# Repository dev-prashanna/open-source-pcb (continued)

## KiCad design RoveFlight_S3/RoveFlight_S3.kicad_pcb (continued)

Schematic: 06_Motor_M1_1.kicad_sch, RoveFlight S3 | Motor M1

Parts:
C110: 100nF; C_0402_1005Metric_RF_C110; MPN GRM155R71C104KA88D
D3: SS24; D_SMA; MPN SS24-13-F
J3: M1 MOTOR; MotorPads; MPN PCB_SOLDER_PADS_24AWG
Q3: AO3400A; SOT-23; MPN AO3400A
R109: 100; R_0402_1005Metric_RF_R109; MPN RC0402FR-071000L
R110: 10k; R_0402_1005Metric_RF_R110; MPN RC0402FR-071002L
R111: 100k; R_0402_1005Metric_RF_R111; MPN RC0402FR-071003L

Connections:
BUF_M1: R109.1; also elsewhere on the board
GATE_M1: Q3.1 (G), R109.2, R110.1
GND: C110.2, Q3.2 (S), R110.2, R111.2; also elsewhere on the board
M1_NEG: D3.2 (A), J3.2, Q3.3 (D)
PWM_M1: R111.1; also elsewhere on the board
VM: C110.1, D3.1 (K), J3.1; also elsewhere on the board

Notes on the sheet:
1S BRUSHED ONLY. Pin1 VM+, pin2 switched motor negative. 1A running / 2A brief stall target. 100R gate resistor; 10k gate-source pulldown; SS24 flyback cathode VM, anode drain. Fit additional 100nF directly at motor terminals; twist leads. Rotation is set by motor wiring.

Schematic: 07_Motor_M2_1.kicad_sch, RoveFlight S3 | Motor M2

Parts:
C111: 100nF; C_0402_1005Metric_RF_C111; MPN GRM155R71C104KA88D
D4: SS24; D_SMA; MPN SS24-13-F
J4: M2 MOTOR; MotorPads; MPN PCB_SOLDER_PADS_24AWG
Q4: AO3400A; SOT-23; MPN AO3400A
R112: 100; R_0402_1005Metric_RF_R112; MPN RC0402FR-071000L
R113: 10k; R_0402_1005Metric_RF_R113; MPN RC0402FR-071002L
R114: 100k; R_0402_1005Metric_RF_R114; MPN RC0402FR-071003L

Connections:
BUF_M2: R112.1; also elsewhere on the board
GATE_M2: Q4.1 (G), R112.2, R113.1
GND: C111.2, Q4.2 (S), R113.2, R114.2; also elsewhere on the board
M2_NEG: D4.2 (A), J4.2, Q4.3 (D)
PWM_M2: R114.1; also elsewhere on the board
VM: C111.1, D4.1 (K), J4.1; also elsewhere on the board

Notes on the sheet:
1S BRUSHED ONLY. Pin1 VM+, pin2 switched motor negative. 1A running / 2A brief stall target. 100R gate resistor; 10k gate-source pulldown; SS24 flyback cathode VM, anode drain. Fit additional 100nF directly at motor terminals; twist leads. Rotation is set by motor wiring.

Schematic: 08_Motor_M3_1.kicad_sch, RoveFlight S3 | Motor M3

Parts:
C112: 100nF; C_0402_1005Metric_RF_C112; MPN GRM155R71C104KA88D
D5: SS24; D_SMA; MPN SS24-13-F
J5: M3 MOTOR; MotorPads; MPN PCB_SOLDER_PADS_24AWG
Q5: AO3400A; SOT-23; MPN AO3400A
R115: 100; R_0402_1005Metric_RF_R115; MPN RC0402FR-071000L
R116: 10k; R_0402_1005Metric_RF_R116; MPN RC0402FR-071002L
R117: 100k; R_0402_1005Metric_RF_R117; MPN RC0402FR-071003L

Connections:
BUF_M3: R115.1; also elsewhere on the board
GATE_M3: Q5.1 (G), R115.2, R116.1
GND: C112.2, Q5.2 (S), R116.2, R117.2; also elsewhere on the board
M3_NEG: D5.2 (A), J5.2, Q5.3 (D)
PWM_M3: R117.1; also elsewhere on the board
VM: C112.1, D5.1 (K), J5.1; also elsewhere on the board

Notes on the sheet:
1S BRUSHED ONLY. Pin1 VM+, pin2 switched motor negative. 1A running / 2A brief stall target. 100R gate resistor; 10k gate-source pulldown; SS24 flyback cathode VM, anode drain. Fit additional 100nF directly at motor terminals; twist leads. Rotation is set by motor wiring.

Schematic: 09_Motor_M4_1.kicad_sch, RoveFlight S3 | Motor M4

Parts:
C113: 100nF; C_0402_1005Metric_RF_C113; MPN GRM155R71C104KA88D
D6: SS24; D_SMA; MPN SS24-13-F
J6: M4 MOTOR; MotorPads; MPN PCB_SOLDER_PADS_24AWG
Q6: AO3400A; SOT-23; MPN AO3400A
R118: 100; R_0402_1005Metric_RF_R118; MPN RC0402FR-071000L
R119: 10k; R_0402_1005Metric_RF_R119; MPN RC0402FR-071002L
R120: 100k; R_0402_1005Metric_RF_R120; MPN RC0402FR-071003L

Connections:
BUF_M4: R118.1; also elsewhere on the board
GATE_M4: Q6.1 (G), R118.2, R119.1
GND: C113.2, Q6.2 (S), R119.2, R120.2; also elsewhere on the board
M4_NEG: D6.2 (A), J6.2, Q6.3 (D)
PWM_M4: R120.1; also elsewhere on the board
VM: C113.1, D6.1 (K), J6.1; also elsewhere on the board

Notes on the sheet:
1S BRUSHED ONLY. Pin1 VM+, pin2 switched motor negative. 1A running / 2A brief stall target. 100R gate resistor; 10k gate-source pulldown; SS24 flyback cathode VM, anode drain. Fit additional 100nF directly at motor terminals; twist leads. Rotation is set by motor wiring.

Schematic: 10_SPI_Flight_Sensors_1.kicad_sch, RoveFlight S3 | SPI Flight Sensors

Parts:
C114: 100nF; C_0402_1005Metric_RF_C114; MPN GRM155R71C104KA88D
C115: 100nF; C_0402_1005Metric_RF_C115; MPN GRM155R71C104KA88D
C116: 1uF; C_0402_1005Metric_RF_C116; MPN GRM155R61A105KE15D
C117: 100nF; C_0402_1005Metric_RF_C117; MPN GRM155R71C104KA88D
C118: 100nF; C_0402_1005Metric_RF_C118; MPN GRM155R71C104KA88D
U8: BMI270; Bosch_LGA-14_3x2.5mm_P0.5mm; MPN BMI270
U9: BMP390; BMP390_LGA10; MPN BMP390

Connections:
+3V3_SENS: C114.1, C115.1, C116.1, C117.1, C118.1, U8.5 (VDDIO), U8.8 (VDD), U9.1 (VDDIO), U9.10 (VDD); also elsewhere on the board
BARO_CS: U9.6 (CSB); also elsewhere on the board
GND: C114.2, C115.2, C116.2, C117.2, C118.2, U8.6 (GNDIO), U8.7 (GND), U9.3 (GND), U9.8 (GND), U9.9 (GND); also elsewhere on the board
IMU_CS: U8.12 (CSB); also elsewhere on the board
IMU_INT: U8.4 (INT1); also elsewhere on the board
SPI_MISO: U8.1 (SDO), U9.5 (SDO); also elsewhere on the board
SPI_MOSI: U8.14 (SDI), U9.4 (SDI); also elsewhere on the board
SPI_SCK: U8.13 (SCK), U9.2 (SCK); also elsewhere on the board

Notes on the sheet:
BMI270 primary 4-wire SPI, INT1 data ready. Auxiliary/OIS pins intentionally NC. BMP390 on shared SPI with independent CS; INT unused. Pressure port faces underside. No compass: motor conductors are too close for a defensible uncalibrated onboard heading.

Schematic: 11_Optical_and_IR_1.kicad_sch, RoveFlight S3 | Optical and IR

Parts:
C119: 100nF; C_0402_1005Metric_RF_C119; MPN GRM155R71C104KA88D
C120: 4.7uF; C_0603_1608Metric; MPN GRM188R60J475KE19D
C121: 1uF; C_0402_1005Metric_RF_C121; MPN GRM155R61A105KE15D
C122: 100nF; C_0402_1005Metric_RF_C122; MPN GRM155R71C104KA88D
R121: 10k; R_0402_1005Metric_RF_R121; MPN RC0402FR-071002L
R122: 10k; R_0402_1005Metric_RF_R122; MPN RC0402FR-071002L
R123: 2.2k; R_0402_1005Metric_RF_R123; MPN RC0402FR-072201L
R124: 2.2k; R_0402_1005Metric_RF_R124; MPN RC0402FR-072201L
R125: 100; R_0402_1005Metric_RF_R125; MPN RC0402FR-071000L
U10: VL53L1CXV0FY/1; ST_VL53L1x; MPN VL53L1CXV0FY/1
U11: TSOP75438TT; MPN TSOP75438TT

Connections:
+3V3: R125.1; also elsewhere on the board
+3V3_SENS: C119.1, C120.1, R121.1, R122.1, R123.1, R124.1, U10.1 (AVDDVCSEL), U10.11 (AVDD); also elsewhere on the board
GND: C119.2, C120.2, C121.2, C122.2, U10.2 (AVSSVCSEL), U10.3 (GND), U10.4 (GND), U10.6 (GND), U10.12 (GND), U11.1 (GND), U11.4 (GND); also elsewhere on the board
I2C_SCL: R124.2, U10.10 (SCL); also elsewhere on the board
I2C_SDA: R123.2, U10.9 (SDA); also elsewhere on the board
IR_RX: U11.3 (OUT); also elsewhere on the board
IR_VS: C121.1, C122.1, R125.2, U11.2 (VS)
TOF_INT: R122.2, U10.7 (GPIO1); also elsewhere on the board
TOF_XSHUT: R121.2, U10.5 (XSHUT); also elsewhere on the board

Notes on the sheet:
VL53L1X faces DOWN, I2C 0x29. Firmware must enable 2V8 I/O mode for 3V3 supply. Use near-ground ranging only; sunlight, reflective floors, tilt and prop wash limit reliability. TSOP75438TT is a 38kHz receiver, not proximity sensing. Optical flow is an external SPI module.

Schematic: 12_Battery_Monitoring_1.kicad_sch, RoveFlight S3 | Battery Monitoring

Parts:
C123: 100nF; C_0402_1005Metric_RF_C123; MPN GRM155R71C104KA88D
C124: 100nF; C_0402_1005Metric_RF_C124; MPN GRM155R71C104KA88D
C125: 100nF; C_0402_1005Metric_RF_C125; MPN GRM155R71C104KA88D
R126: 1k; R_0402_1005Metric_RF_R126; MPN RC0402FR-071001L
R127: 100k; R_0402_1005Metric_RF_R127; MPN RC0402FR-071003L
R128: 100k; R_0402_1005Metric_RF_R128; MPN RC0402FR-071003L
R129: 1k; R_0402_1005Metric_RF_R129; MPN RC0402FR-071001L
U12: INA180A2IDBVR; SOT-23-5; MPN INA180A2IDBVR

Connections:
+3V3: C123.1, U12.5 (V+); also elsewhere on the board
BAT_ADC: C125.1, R129.2; also elsewhere on the board
BAT_DIV: R127.2, R128.1, R129.1
BAT_PROTECTED: U12.3 (+); also elsewhere on the board
CURRENT_ADC: C124.1, R126.2; also elsewhere on the board
CURRENT_RAW: R126.1, U12.1
GND: C123.2, C124.2, C125.2, R128.2, U12.2 (GND); also elsewhere on the board
VM: R127.1, U12.4 (-); also elsewhere on the board

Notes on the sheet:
Kelvin sense R1, 5mOhm. INA180A2 gain50: 0.25V/A. ADC1 GPIO1. Battery ADC1 GPIO2, 1:2 divider, RC filter. Calibrate ADC offset/gain in firmware. Fuse is backup short-circuit protection; firmware must implement current and low-battery shutdown.

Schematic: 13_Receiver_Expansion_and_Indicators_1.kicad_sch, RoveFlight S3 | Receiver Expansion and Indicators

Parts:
D7: GREEN; LED_0402_1005Metric; MPN 150040GS73240
J7: RC 3V3; JST_SH_SM04B-SRSS-TB_1x04-1MP_P1.00mm_Horizontal; MPN SM04B-SRSS-TB(LF)(SN)
J8: OPTICAL FLOW SPI; JST_SH_SM07B-SRSS-TB_1x07-1MP_P1.00mm_Horizontal; MPN SM07B-SRSS-TB(LF)(SN)
J9: DEBUG UART; JST_SH_SM06B-SRSS-TB_1x06-1MP_P1.00mm_Horizontal; MPN SM06B-SRSS-TB(LF)(SN)
J10: I2C 3V3; JST_SH_SM04B-SRSS-TB_1x04-1MP_P1.00mm_Horizontal; MPN SM04B-SRSS-TB(LF)(SN)
R130: 1k; R_0402_1005Metric_RF_R130; MPN RC0402FR-071001L
TP1: +3V3; ProbePad; MPN PCB_TEST_PAD
TP2: GND; ProbePad; MPN PCB_TEST_PAD
TP3: VM; ProbePad; MPN PCB_TEST_PAD
TP4: I2C_SDA; ProbePad; MPN PCB_TEST_PAD
TP5: I2C_SCL; ProbePad; MPN PCB_TEST_PAD
TP6: SPI_SCK; ProbePad; MPN PCB_TEST_PAD
TP7: SPI_MOSI; ProbePad; MPN PCB_TEST_PAD
TP8: SPI_MISO; ProbePad; MPN PCB_TEST_PAD
TP9: DEBUG_TX; ProbePad; MPN PCB_TEST_PAD
TP10: DEBUG_RX; ProbePad; MPN PCB_TEST_PAD
TP11: PWM_M1; ProbePad; MPN PCB_TEST_PAD
TP12: PWM_M2; ProbePad; MPN PCB_TEST_PAD
TP13: PWM_M3; ProbePad; MPN PCB_TEST_PAD
TP14: PWM_M4; ProbePad; MPN PCB_TEST_PAD

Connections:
+3V3: J7.2, J8.2, J9.2, TP1.1; also elsewhere on the board
+3V3_SENS: J10.2; also elsewhere on the board
BOOT: J9.6; also elsewhere on the board
DEBUG_RX: J9.4, TP10.1; also elsewhere on the board
DEBUG_TX: J9.3, TP9.1; also elsewhere on the board
EN: J9.5; also elsewhere on the board
FLOW_CS: J8.6; also elsewhere on the board
FLOW_INT: J8.7; also elsewhere on the board
GND: D7.1 (K), J7.1, J8.1, J9.1, J10.1, TP2.1; also elsewhere on the board
I2C_SCL: J10.4, TP5.1; also elsewhere on the board
I2C_SDA: J10.3, TP4.1; also elsewhere on the board
LED_A: D7.2 (A), R130.2
PWM_M1: TP11.1; also elsewhere on the board
PWM_M2: TP12.1; also elsewhere on the board
PWM_M3: TP13.1; also elsewhere on the board
PWM_M4: TP14.1; also elsewhere on the board
RC_RX: J7.3; also elsewhere on the board
RC_TX: J7.4; also elsewhere on the board
SPI_MISO: J8.5, TP8.1; also elsewhere on the board
SPI_MOSI: J8.4, TP7.1; also elsewhere on the board
SPI_SCK: J8.3, TP6.1; also elsewhere on the board
STATUS_LED: R130.1; also elsewhere on the board
VM: TP3.1; also elsewhere on the board

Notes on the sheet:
Receiver: 3V3 UART CRSF/iBUS only, no 5V tolerance or onboard SBUS inverter. External PMW3901 breakout must include its required regulator/level compatibility and lens. SPI test pads/flow connector are 3V3; sensor SPI max10MHz, initial firmware 1MHz.

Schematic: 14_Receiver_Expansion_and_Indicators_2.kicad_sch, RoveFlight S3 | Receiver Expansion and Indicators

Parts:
TP15: SAFE_CLR_N; ProbePad; MPN PCB_TEST_PAD
TP16: ARMED; ProbePad; MPN PCB_TEST_PAD

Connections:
ARMED: TP16.1; also elsewhere on the board
SAFE_CLR_N: TP15.1; also elsewhere on the board

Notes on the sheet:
Receiver: 3V3 UART CRSF/iBUS only, no 5V tolerance or onboard SBUS inverter. External PMW3901 breakout must include its required regulator/level compatibility and lens. SPI test pads/flow connector are 3V3; sensor SPI max10MHz, initial firmware 1MHz.

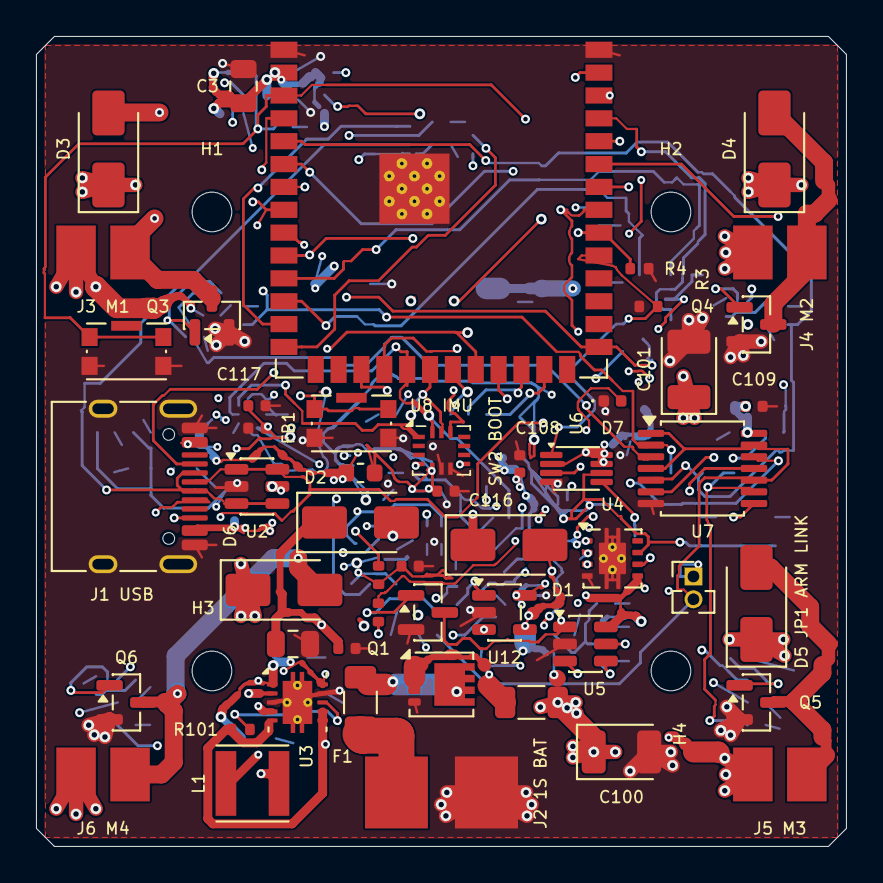
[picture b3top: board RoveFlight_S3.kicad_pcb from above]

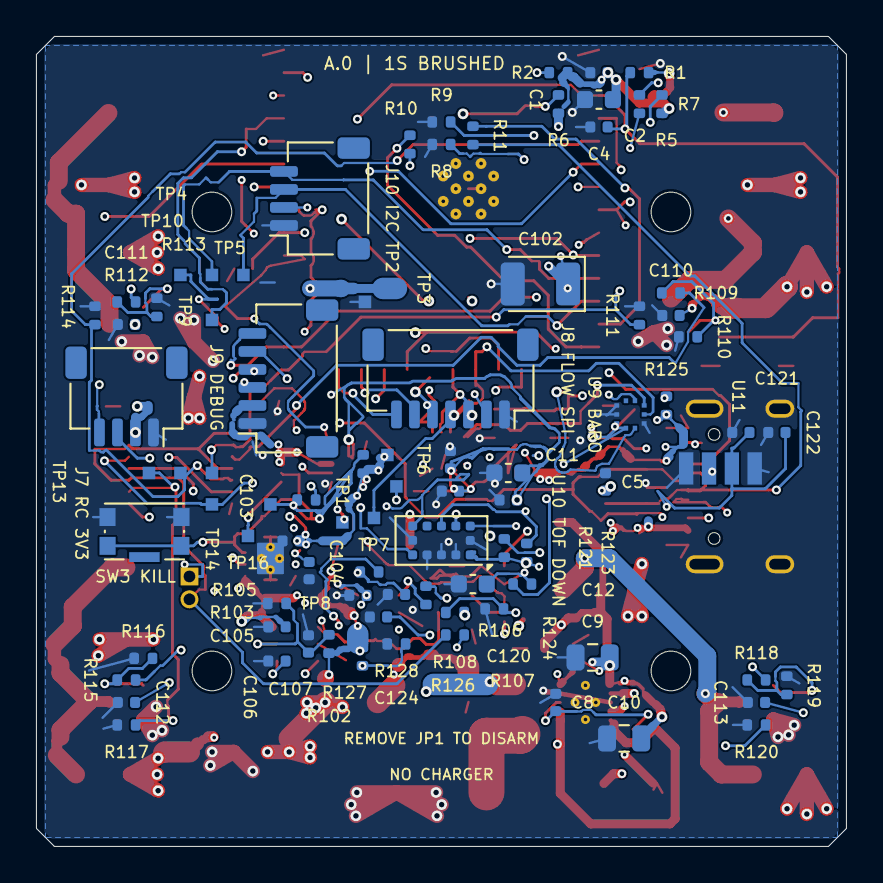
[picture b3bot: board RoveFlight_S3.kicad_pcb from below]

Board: 6 copper layers, 45.0 x 45.0 mm, 142 parts (87 on the bottom side), 71 nets.

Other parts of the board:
H1, H2, H3, H4: MountingHole_2.2mm_M2

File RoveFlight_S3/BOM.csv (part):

Reference,Value,MPN,Manufacturer,Footprint,Section,Datasheet
U1,ESP32-S3-WROOM-1-N8R2,ESP32-S3-WROOM-1-N8R2,Espressif,RoveFlight:ESP32-S3-WROOM-1_Overhang,ESP32S3 Controller,https://www.espressif.com/sites/default/files/documentation/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
C1,100nF,GRM155R71C104KA88D,Murata,RoveFlight:C_0402_1005Metric_RF_C1,ESP32S3 Controller,
C2,10uF,GRM188R60J106ME47D,Murata,Capacitor_SMD:C_0603_1608Metric,ESP32S3 Controller,
C3,22uF,GRM21BR60J226ME39L,Murata,Capacitor_SMD:C_0805_2012Metric,ESP32S3 Controller,
R1,10k,RC0402FR-071002L,Yageo,RoveFlight:R_0402_1005Metric_RF_R1,ESP32S3 Controller,
C4,1uF,GRM155R61A105KE15D,Murata,RoveFlight:C_0402_1005Metric_RF_C4,ESP32S3 Controller,
R2,10k,RC0402FR-071002L,Yageo,RoveFlight:R_0402_1005Metric_RF_R2,ESP32S3 Controller,
SW1,RESET,KMR221GLFS,C&K,Button_Switch_SMD:SW_Push_1P1T-SH_NO_CK_KMR2xxG,ESP32S3 Controller,
SW2,BOOT,KMR221GLFS,C&K,Button_Switch_SMD:SW_Push_1P1T-SH_NO_CK_KMR2xxG,ESP32S3 Controller,
SW3,KILL,KMR221GLFS,C&K,Button_Switch_SMD:SW_Push_1P1T-SH_NO_CK_KMR2xxG,ESP32S3 Controller,
R3,100k,RC0402FR-071003L,Yageo,RoveFlight:R_0402_1005Metric_RF_R3,ESP32S3 Controller,
R4,100k,RC0402FR-071003L,Yageo,RoveFlight:R_0402_1005Metric_RF_R4,ESP32S3 Controller,
R5,10k,RC0402FR-071002L,Yageo,RoveFlight:R_0402_1005Metric_RF_R5,ESP32S3 Controller,
R6,10k,RC0402FR-071002L,Yageo,RoveFlight:R_0402_1005Metric_RF_R6,ESP32S3 Controller,
R7,10k,RC0402FR-071002L,Yageo,RoveFlight:R_0402_1005Metric_RF_R7,ESP32S3 Controller,
J1,USB-C,TYPE-C-31-M-12,HRO,Connector_USB:USB_C_Receptacle_HRO_TYPE-C-31-M-12,USB Programming,
R8,5.1k,RC0402FR-075101L,Yageo,RoveFlight:R_0402_1005Metric_RF_R8,USB Programming,
R9,5.1k,RC0402FR-075101L,Yageo,RoveFlight:R_0402_1005Metric_RF_R9,USB Programming,
R10,22,RC0402FR-0722R0L,Yageo,RoveFlight:R_0402_1005Metric_RF_R10,USB Programming,
R11,22,RC0402FR-0722R0L,Yageo,RoveFlight:R_0402_1005Metric_RF_R11,USB Programming,
U2,USBLC6-2SC6,USBLC6-2SC6,STMicroelectronics,Package_TO_SOT_SMD:SOT-23-6,USB Programming,https://www.st.com/resource/en/datasheet/usblc6-2.pdf
C5,1uF,GRM155R61A105KE15D,Murata,RoveFlight:C_0402_1005Metric_RF_C5,USB Programming,
J2,1S BATTERY,PCB_SOLDER_PADS_20AWG,PCB,RoveFlight:BatteryPads,Battery Power,
F1,5A fuse,0467005.NR,Littelfuse,Fuse:Fuse_1206_3216Metric,Battery Power,
Q1,DMP2008UFG-7,DMP2008UFG-7,Diodes Inc.,Package_SON:Diodes_PowerDI3333-8,Battery Power,https://www.diodes.com/datasheet/download/DMP2008UFG.pdf
R100,5mOhm 1% 0.25W,WSL1206R0050FEA,Vishay,Resistor_SMD:R_1206_3216Metric,Battery Power,
D1,SS14,SS14-13-F,Diodes Inc.,Diode_SMD:D_SMA,Battery Power,
D2,SS14,SS14-13-F,Diodes Inc.,Diode_SMD:D_SMA,Battery Power,
C6,22uF,GRM21BR60J226ME39L,Murata,Capacitor_SMD:C_0805_2012Metric,Battery Power,
C7,100nF,GRM155R71C104KA88D,Murata,RoveFlight:C_0402_1005Metric_RF_C7,Battery Power,
U3,TPS63001DRCR,TPS63001DRCR,Texas Instruments,RoveFlight:Texas_DRC0010J_ThermalVias_RF_U3,Battery Power,https://www.ti.com/lit/ds/symlink/tps63000.pdf
R101,100,RC0402FR-071000L,Yageo,RoveFlight:R_0402_1005Metric_RF_R101,Battery Power,
C8,100nF,GRM155R71C104KA88D,Murata,RoveFlight:C_0402_1005Metric_RF_C8,Battery Power,
C9,22uF,GRM21BR60J226ME39L,Murata,Capacitor_SMD:C_0805_2012Metric,Battery Power,
C10,22uF,GRM21BR60J226ME39L,Murata,Capacitor_SMD:C_0805_2012Metric,Battery Power,
L1,2.2uH 3A,IFSC1515AHER2R2M01,Vishay,Inductor_SMD:L_Vishay_IFSC-1515AH_4x4x1.8mm,Battery Power,
FB1,600R@100MHz,BLM18AG601SN1D,Murata,Inductor_SMD:L_0603_1608Metric,Battery Power,
C11,10uF,GRM188R60J106ME47D,Murata,Capacitor_SMD:C_0603_1608Metric,Battery Power,
C12,100nF,GRM155R71C104KA88D,Murata,RoveFlight:C_0402_1005Metric_RF_C12,Battery Power,
C100,100uF 6.3V polymer,T520B107M006ATE070,KEMET,Capacitor_Tantalum_SMD:CP_EIA-3528-21_Kemet-B,Battery Power,
C101,100uF 6.3V polymer,T520B107M006ATE070,KEMET,Capacitor_Tantalum_SMD:CP_EIA-3528-21_Kemet-B,Battery Power,
C102,100uF 6.3V logic bulk,T520B107M006ATE070,KEMET,Capacitor_Tantalum_SMD:CP_EIA-3528-21_Kemet-B,Battery Power,
U4,TPS3431SDRBR,TPS3431SDRBR,Texas Instruments,Package_DFN_QFN:Texas_DRB0008A,Motor Safety Interlock,https://www.ti.com/lit/ds/symlink/tps3431.pdf
C103,100nF,GRM155R71C104KA88D,Murata,RoveFlight:C_0402_1005Metric_RF_C103,Motor Safety Interlock,
C104,1nF,GRM1555C1H102JA01D,Murata,RoveFlight:C_0402_1005Metric_RF_C104,Motor Safety Interlock,
U5,TPS3808G01DBVR,TPS3808G01DBVR,Texas Instruments,Package_TO_SOT_SMD:SOT-23-6,Motor Safety Interlock,https://www.ti.com/lit/ds/symlink/tps3808.pdf
C105,100nF,GRM155R71C104KA88D,Murata,RoveFlight:C_0402_1005Metric_RF_C105,Motor Safety Interlock,
C106,10nF,GRM155R71H103KA88D,Murata,RoveFlight:C_0402_1005Metric_RF_C106,Motor Safety Interlock,
R102,665k,RC0402FR-076653L,Yageo,RoveFlight:R_0402_1005Metric_RF_R102,Motor Safety Interlock,
R103,100k,RC0402FR-071003L,Yageo,RoveFlight:R_0402_1005Metric_RF_R103,Motor Safety Interlock,
C107,10nF,GRM155R71H103KA88D,Murata,RoveFlight:C_0402_1005Metric_RF_C107,Motor Safety Interlock,
U6,SN74LVC1G74DCUR,SN74LVC1G74DCUR,Texas Instruments,Package_SO:VSSOP-8_2.3x2mm_P0.5mm,Motor Safety Interlock,https://www.ti.com/lit/ds/symlink/sn74lvc1g74.pdf
C108,100nF,GRM155R71C104KA88D,Murata,RoveFlight:C_0402_1005Metric_RF_C108,Motor Safety Interlock,
R104,10k,RC0402FR-071002L,Yageo,RoveFlight:R_0402_1005Metric_RF_R104,Motor Safety Interlock,
R105,1k,RC0402FR-071001L,Yageo,RoveFlight:R_0402_1005Metric_RF_R105,Motor Safety Interlock,
Q2,2N7002,2N7002,Nexperia,Package_TO_SOT_SMD:SOT-23,Motor Safety Interlock,
R106,100k,RC0402FR-071003L,Yageo,RoveFlight:R_0402_1005Metric_RF_R106,Motor Safety Interlock,
R107,1M,RC0402FR-071004L,Yageo,RoveFlight:R_0402_1005Metric_RF_R107,Motor Safety Interlock,
JP1,REMOVE TO DISARM,20021111-00002T4LF,Amphenol,Connector_PinHeader_1.27mm:PinHeader_1x02_P1.27mm_Vertical,Motor Safety Interlock,
R108,10k,RC0402FR-071002L,Yageo,RoveFlight:R_0402_1005Metric_RF_R108,Motor Safety Interlock,
U7,SN74LVC125APWR,SN74LVC125APWR,Texas Instruments,Package_SO:TSSOP-14_4.4x5mm_P0.65mm,Motor Safety Interlock,https://www.ti.com/lit/ds/symlink/sn74lvc125a.pdf
C109,100nF,GRM155R71C104KA88D,Murata,RoveFlight:C_0402_1005Metric_RF_C109,Motor Safety Interlock,
J3,M1 MOTOR,PCB_SOLDER_PADS_24AWG,PCB,RoveFlight:MotorPads,Motor M1,
Q3,AO3400A,AO3400A,Alpha & Omega,Package_TO_SOT_SMD:SOT-23,Motor M1,https://www.aosmd.com/res/data_sheets/AO3400A.pdf
R109,100,RC0402FR-071000L,Yageo,RoveFlight:R_0402_1005Metric_RF_R109,Motor M1,
R110,10k,RC0402FR-071002L,Yageo,RoveFlight:R_0402_1005Metric_RF_R110,Motor M1,
R111,100k,RC0402FR-071003L,Yageo,RoveFlight:R_0402_1005Metric_RF_R111,Motor M1,
D3,SS24,SS24-13-F,Diodes Inc.,Diode_SMD:D_SMA,Motor M1,
C110,100nF,GRM155R71C104KA88D,Murata,RoveFlight:C_0402_1005Metric_RF_C110,Motor M1,
J4,M2 MOTOR,PCB_SOLDER_PADS_24AWG,PCB,RoveFlight:MotorPads,Motor M2,
Q4,AO3400A,AO3400A,Alpha & Omega,Package_TO_SOT_SMD:SOT-23,Motor M2,https://www.aosmd.com/res/data_sheets/AO3400A.pdf
R112,100,RC0402FR-071000L,Yageo,RoveFlight:R_0402_1005Metric_RF_R112,Motor M2,
R113,10k,RC0402FR-071002L,Yageo,RoveFlight:R_0402_1005Metric_RF_R113,Motor M2,
R114,100k,RC0402FR-071003L,Yageo,RoveFlight:R_0402_1005Metric_RF_R114,Motor M2,
D4,SS24,SS24-13-F,Diodes Inc.,Diode_SMD:D_SMA,Motor M2,
C111,100nF,GRM155R71C104KA88D,Murata,RoveFlight:C_0402_1005Metric_RF_C111,Motor M2,
J5,M3 MOTOR,PCB_SOLDER_PADS_24AWG,PCB,RoveFlight:MotorPads,Motor M3,
Q5,AO3400A,AO3400A,Alpha & Omega,Package_TO_SOT_SMD:SOT-23,Motor M3,https://www.aosmd.com/res/data_sheets/AO3400A.pdf
R115,100,RC0402FR-071000L,Yageo,RoveFlight:R_0402_1005Metric_RF_R115,Motor M3,
R116,10k,RC0402FR-071002L,Yageo,RoveFlight:R_0402_1005Metric_RF_R116,Motor M3,
R117,100k,RC0402FR-071003L,Yageo,RoveFlight:R_0402_1005Metric_RF_R117,Motor M3,
D5,SS24,SS24-13-F,Diodes Inc.,Diode_SMD:D_SMA,Motor M3,
C112,100nF,GRM155R71C104KA88D,Murata,RoveFlight:C_0402_1005Metric_RF_C112,Motor M3,
J6,M4 MOTOR,PCB_SOLDER_PADS_24AWG,PCB,RoveFlight:MotorPads,Motor M4,
Q6,AO3400A,AO3400A,Alpha & Omega,Package_TO_SOT_SMD:SOT-23,Motor M4,https://www.aosmd.com/res/data_sheets/AO3400A.pdf
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
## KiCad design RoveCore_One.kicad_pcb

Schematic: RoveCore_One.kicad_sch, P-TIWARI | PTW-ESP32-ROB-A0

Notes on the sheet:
P-TIWARI / Plug in, program, and build. A.0 engineering prototype: see docs/Manufacturing_Readiness.md before fabrication. Protected 2S battery; external balance charger. USB powers logic only. Global nets join functional sheets. Four-layer board; 80 x 65 mm nominal.

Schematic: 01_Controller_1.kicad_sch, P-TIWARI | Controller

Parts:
C1: 100nF 16V; C_0603_1608Metric; MPN GRM188R71C104KA01D
C2: 22uF 10V; C_0805_2012Metric; MPN GRM21BR61A226ME44L
C3: 1uF 16V; C_0603_1608Metric; MPN GRM188R61C105KA12D
J1: SERVICE 3V3; PinHeader_1x06_P2.00mm_Vertical; MPN M22-2010605
R1, R2, R3, R4, R5: 10k; R_0603_1608Metric; MPN RC0603FR-0710KL
R6: 100k; R_0603_1608Metric; MPN RC0603FR-07100KL
SW1: SW1; SW_Push_1P1T-SH_NO_CK_KMR2xxG; MPN KMR221GLFS
SW2: SW2; SW_Push_1P1T-SH_NO_CK_KMR2xxG; MPN KMR221GLFS
U1: ESP32-WROOM-32E-N8; ESP32-WROOM-32E_Board; MPN ESP32-WROOM-32E-N8

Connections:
+3V3: C1.1, C2.1, J1.2, R1.1, R2.1, R4.1, R5.1, U1.2 (VDD); also elsewhere on the board
BAT_ADC: U1.9 (IO33); also elsewhere on the board
BOOT: J1.6, R2.2, SW2.1, U1.25 (IO0); also elsewhere on the board
BUZZ_PWM: R6.1, U1.24 (IO2); also elsewhere on the board
EN: C3.1, J1.5, R1.2, SW1.1, U1.3 (EN); also elsewhere on the board
ENC_LA: U1.4 (SENSOR_VP); also elsewhere on the board
ENC_LB: U1.5 (SENSOR_VN); also elsewhere on the board
ENC_RA: U1.6 (IO34); also elsewhere on the board
ENC_RB: U1.7 (IO35); also elsewhere on the board
GND: C1.2, C2.2, C3.2, J1.1, R3.2, R6.2, SW1.2, SW2.2, U1.1, U1.15, U1.38, U1.39, U1.[1,15,38,39] (GND); also elsewhere on the board
I2C_SCL: U1.36 (IO22); also elsewhere on the board
I2C_SDA: U1.33 (IO21); also elsewhere on the board
IMU_INT: U1.8 (IO32); also elsewhere on the board
M_A1: U1.10 (IO25); also elsewhere on the board
M_A2: U1.11 (IO26); also elsewhere on the board
M_B1: U1.12 (IO27); also elsewhere on the board
M_B2: U1.13 (IO14); also elsewhere on the board
SERVO_OE: R5.2, U1.23 (IO15); also elsewhere on the board
SPI_CS: R4.2, U1.29 (IO5); also elsewhere on the board
SPI_MISO: U1.31 (IO19); also elsewhere on the board
SPI_MOSI: U1.37 (IO23); also elsewhere on the board
SPI_SCK: U1.30 (IO18); also elsewhere on the board
STRAP12: R3.1, U1.14 (IO12)
U0_RX: J1.4, U1.34 (RXD0/IO3); also elsewhere on the board
U0_TX: J1.3, U1.35 (TXD0/IO1); also elsewhere on the board
UART_RX: U1.27 (IO16); also elsewhere on the board
UART_TX: U1.28 (IO17); also elsewhere on the board
US_ECHO: U1.16 (IO13); also elsewhere on the board
US_TRIG: U1.26 (IO4); also elsewhere on the board

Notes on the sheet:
ESP32-WROOM-32E-N8: 8 MB flash; no PSRAM; USB bridge required. GPIO34/35/36/39 input only. GPIO12 held LOW for 3.3V flash. Boot: hold BOOT, tap RESET. All allocated GPIO are accessible at headers/test pads; shared signals are not free outputs.

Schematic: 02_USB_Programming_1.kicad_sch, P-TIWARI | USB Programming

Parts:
C4: 1uF 16V; C_0603_1608Metric; MPN GRM188R61C105KA12D
C5, C6: 100nF 16V; C_0603_1608Metric; MPN GRM188R71C104KA01D
C7: 4.7uF 10V; C_0603_1608Metric; MPN GRM188R61A475KE15D
J2: USB-C 5V DATA; USB_C_Receptacle_HRO_TYPE-C-31-M-12; MPN TYPE-C-31-M-12
Q1, Q2: MMBT3904; SOT-23; MPN MMBT3904
R7, R8: 5.1k; R_0603_1608Metric; MPN RC0603FR-075K1L
R9: 1k; R_0603_1608Metric; MPN RC0603FR-071KL
R10: 22.1k; R_0603_1608Metric; MPN RC0603FR-0722K1L
R11: 47.5k; R_0603_1608Metric; MPN RC0603FR-0747K5L
R12, R13: 10k; R_0603_1608Metric; MPN RC0603FR-0710KL
U2: CP2102N-A02-GQFN24; QFN-24-1EP_4x4mm_P0.5mm_EP2.6x2.6mm; MPN CP2102N-A02-GQFN24
U3: USBLC6-2SC6; SOT-23-6; MPN USBLC6-2SC6

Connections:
+3V3: C5.1, C6.1, C7.1, R9.1, U2.5 (VIO), U2.6 (VDD), U2.7 (VREGIN); also elsewhere on the board
AUTO_BOOT_B: Q2.1 (B), R13.2
AUTO_EN_B: Q1.1 (B), R12.2
BOOT: Q2.3 (C); also elsewhere on the board
CC1: J2.A5 (CC1), R7.1
CC2: J2.B5 (CC2), R8.1
DTR: Q2.2 (E), R12.1, U2.23 (~DTR)
EN: Q1.3 (C); also elsewhere on the board
GND: C4.2, C5.2, C6.2, C7.2, J2.A1 (GND), J2.A12 (GND), J2.B1 (GND), J2.B12 (GND), J2.SH (SHIELD), R7.2, R8.2, R11.2, U2.2 (GND), U2.25 (GND), U3.2 (GND); also elsewhere on the board
RTS: Q1.2 (E), R13.1, U2.19 (~RTS)
U0_RX: U2.21 (TXD); also elsewhere on the board
U0_TX: U2.20 (RXD); also elsewhere on the board
USB_DM: J2.A7 (D-), J2.B7 (D-), U2.4 (D-), U3.3 (I/O2), U3.4 (I/O2)
USB_DP: J2.A6 (D+), J2.B6 (D+), U2.3 (D+), U3.1 (I/O1), U3.6 (I/O1)
USB_RST: R9.2, U2.9 (~RST)
USB_VBUS: C4.1, J2.A4 (VBUS), J2.A9 (VBUS), J2.B4 (VBUS), J2.B9 (VBUS), R10.1, U3.5 (VBUS); also elsewhere on the board
VBUS_SENSE: R10.2, R11.1, U2.8 (VBUS)

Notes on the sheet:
Self-powered CP2102N: VREGIN, VDD and VIO tied to 3V3 per Silicon Labs. VBUS sensing uses 22.1k / 47.5k divider. Dual 5.1k CC pulldowns: 5V sink, no PD. USB supplies LOGIC ONLY. Firmware must respect the host current entitlement.

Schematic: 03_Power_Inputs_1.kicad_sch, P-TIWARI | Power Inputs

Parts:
C8: 470uF 16V; CP_Elec_8x10.5; MPN EEE-FK1C471P
C9, C11: 100nF 16V; C_0603_1608Metric; MPN GRM188R71C104KA01D
C10: 22uF 10V; C_0805_2012Metric; MPN GRM21BR61A226ME44L
D1, D2, D3: SS34; D_SMA; MPN SS34
F1: 2A hold; Fuse_1812_4532Metric; MPN 1812L200/16DR
F2: 1.1A hold; Fuse_1812_4532Metric; MPN 1812L110/16DR
F3: 0.5A hold; Fuse_1812_4532Metric; MPN 1812L050/24DR
J3: 2S BAT 6.4-8.4V; TerminalBlock_Phoenix_PT-1,5-2-3.5-H_1x02_P3.50mm_Horizontal; MPN 1984617
J4: EXT 5V LOGIC; TerminalBlock_Phoenix_PT-1,5-2-3.5-H_1x02_P3.50mm_Horizontal; MPN 1984617
Q3: AO3401A; SOT-23; MPN AO3401A
R14, R15: 100k; R_0603_1608Metric; MPN RC0603FR-07100KL
R16: 33k; R_0603_1608Metric; MPN RC0603FR-0733KL
R17: 1k; R_0603_1608Metric; MPN RC0603FR-071KL

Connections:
BAT5: D3.2 (A); also elsewhere on the board
BAT_ADC: C11.1, R17.2; also elsewhere on the board
BAT_DIV: R15.2, R16.1, R17.1
BAT_FUSED: F1.2, Q3.3 (D)
BAT_RAW: F1.1, J3.1
EXT5_FUSED: D1.2 (A), F2.2
EXT5_RAW: F2.1, J4.1
GND: C8.2, C9.2, C10.2, C11.2, J3.2, J4.2, R14.2, R16.2; also elsewhere on the board
LOGIC5: C10.1, D1.1 (K), D2.1 (K), D3.1 (K); also elsewhere on the board
Q3_G: Q3.1 (G), R14.1
USB_FUSED: D2.2 (A), F3.2
USB_VBUS: F3.1; also elsewhere on the board
VBAT: C8.1, C9.1, Q3.2 (S), R15.1; also elsewhere on the board

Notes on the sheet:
2S pack MUST include cell-level protection, overcurrent cutoff and balancing. NO onboard charger: disconnect pack and charge with a proper 2S balance charger. Schottky source OR prevents backfeeding USB/external/battery logic sources. Common ground.

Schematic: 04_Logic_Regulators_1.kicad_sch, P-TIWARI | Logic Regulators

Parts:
C12, C14, C17, C19: 100nF 16V; C_0603_1608Metric; MPN GRM188R71C104KA01D
C13, C18: 10uF 16V; C_0805_2012Metric; MPN GRM21BR61C106KE15L
C15, C16, C20, C21: 22uF 10V; C_0805_2012Metric; MPN GRM21BR61A226ME44L
C22: 4.7uF 10V; C_0603_1608Metric; MPN GRM188R61A475KE15D
FB1: 600R @100MHz; L_0603_1608Metric; MPN BLM18AG601SN1D
L1, L2: 4.7uH; L_Bourns_SRP5030T; MPN SRP5030T-4R7M
R18, R20, R21: 100k; R_0603_1608Metric; MPN RC0603FR-07100KL
R19: 27.4k; R_0603_1608Metric; MPN RC0603FR-0727K4L
U4: AP63205WU-7; TSOT-23-6; MPN AP63205WU-7
U5: AP63203WU-7; TSOT-23-6; MPN AP63203WU-7

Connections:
+3V3: C20.1, C21.1, FB1.1, L2.2, U5.1 (FB); also elsewhere on the board
+3V3_SENS: C22.1, FB1.2; also elsewhere on the board
BAT5: C15.1, C16.1, L1.2, U4.1 (FB); also elsewhere on the board
GND: C13.2, C14.2, C15.2, C16.2, C18.2, C19.2, C20.2, C21.2, C22.2, R19.2, R21.2, U4.4 (GND), U5.4 (GND); also elsewhere on the board
LOGIC5: C18.1, C19.1, R20.1, U5.3 (IN); also elsewhere on the board
SW_3V3: C17.2, L2.1, U5.5 (SW)
SW_BAT: C12.2, L1.1, U4.5 (SW)
U4_BST: C12.1, U4.6 (BST)
U4_EN: R18.2, R19.1, U4.2 (EN)
U5_BST: C17.1, U5.6 (BST)
U5_EN: R20.2, R21.1, U5.2 (EN)
VBAT: C13.1, C14.1, R18.1, U4.3 (IN); also elsewhere on the board

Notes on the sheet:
AP63205 battery buck 5V; AP63203 logic buck 3V3. Feedback on output side of inductors. Battery EN divider 100k/27.4k: nominal rising UVLO about 5.6V, NOT cell protection. 3V3 target 1A total, sensor/expansion budget 150mA. Quiet sensor branch uses ferrite + local caps.

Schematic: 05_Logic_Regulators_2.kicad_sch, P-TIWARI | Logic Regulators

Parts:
C23: 100nF 16V; C_0603_1608Metric; MPN GRM188R71C104KA01D
R22, R23: 2.2k; R_0603_1608Metric; MPN RC0603FR-072K2L

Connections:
+3V3: R22.1, R23.1; also elsewhere on the board
+3V3_SENS: C23.1; also elsewhere on the board
GND: C23.2; also elsewhere on the board
I2C_SCL: R23.2; also elsewhere on the board
I2C_SDA: R22.2; also elsewhere on the board

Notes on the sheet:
AP63205 battery buck 5V; AP63203 logic buck 3V3. Feedback on output side of inductors. Battery EN divider 100k/27.4k: nominal rising UVLO about 5.6V, NOT cell protection. 3V3 target 1A total, sensor/expansion budget 150mA. Quiet sensor branch uses ferrite + local caps.

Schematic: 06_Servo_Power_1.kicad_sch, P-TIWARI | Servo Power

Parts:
C24: 100nF 16V; C_0603_1608Metric; MPN GRM188R71C104KA01D
C25, C26: 10uF 16V; C_0805_2012Metric; MPN GRM21BR61C106KE15L
C27: 75pF 50V; C_0603_1608Metric; MPN GRM1885C1H750JA01D
C28, C29: 22uF 10V; C_0805_2012Metric; MPN GRM21BR61A226ME44L
C30: 470uF 16V; CP_Elec_8x10.5; MPN EEE-FK1C471P
F4: 2A hold; Fuse_1812_4532Metric; MPN 1812L200/16DR
J5: SERVO EXT 5-6V; TerminalBlock_Phoenix_PT-1,5-2-3.5-H_1x02_P3.50mm_Horizontal; MPN 1984617
JP1: SERVO SELECT 1-2 BAT / 2-3 EXT; PinHeader_1x03_P2.54mm_Vertical; MPN 61300311121
L3: 10uH; L_Bourns_SRP5030T; MPN SRP5030T-100M
Q4: AO3401A; SOT-23; MPN AO3401A
R24, R26, R28: 100k; R_0603_1608Metric; MPN RC0603FR-07100KL
R25: 27.4k; R_0603_1608Metric; MPN RC0603FR-0727K4L
R27: 13.3k; R_0603_1608Metric; MPN RC0603FR-0713K3L
U6: TPS54302DDCR; SOT-23-6; MPN TPS54302DDCR

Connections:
GND: C25.2, C26.2, C28.2, C29.2, C30.2, J5.2, R25.2, R27.2, R28.2, U6.1 (GND); also elsewhere on the board
Q4_G: Q4.1 (G), R28.1
SERVO5: C30.1, F4.2; also elsewhere on the board
SERVO_BOOT: C24.1, U6.6 (BOOT)
SERVO_BUCK: C27.1, C28.1, C29.1, JP1.1, L3.2, R26.1
SERVO_EN: R24.2, R25.1, U6.5 (EN)
SERVO_EXT: JP1.3, Q4.2 (S)
SERVO_EXT_RAW: J5.1, Q4.3 (D)
SERVO_FB: C27.2, R26.2, R27.1, U6.4 (FB)
SERVO_SELECTED: F4.1, JP1.2
SW_SERVO: C24.2, L3.1, U6.2 (SW)
VBAT: C25.1, C26.1, R24.1, U6.3 (VIN); also elsewhere on the board

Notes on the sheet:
Servo source selector: fit ONE shunt only. Never bridge both supplies. TPS54302 nominal Vout = 0.596*(1+100/13.3) = 5.077V. 10uH, 44uF ceramic, 75pF feedforward. Servo recommendation: 2A total continuous, 3A brief peak ONLY after thermal validation. Four small servos, not four stall currents.

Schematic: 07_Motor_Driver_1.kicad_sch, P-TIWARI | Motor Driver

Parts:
C31: 10nF 25V; C_0603_1608Metric; MPN GRM188R71E103KA01D
C32: 2.2uF 10V; C_0603_1608Metric; MPN GRM188R61A225KE34D
C33: 100nF 16V; C_0603_1608Metric; MPN GRM188R71C104KA01D
C34: 10uF 16V; C_0805_2012Metric; MPN GRM21BR61C106KE15L
C35: 470uF 16V; CP_Elec_8x10.5; MPN EEE-FK1C471P
F5: 2A hold; Fuse_1812_4532Metric; MPN 1812L200/16DR
J6: VM 3-8.4V; TerminalBlock_Phoenix_PT-1,5-2-3.5-H_1x02_P3.50mm_Horizontal; MPN 1984617
J7: MOTOR A; TerminalBlock_Phoenix_PT-1,5-2-3.5-H_1x02_P3.50mm_Horizontal; MPN 1984617
J8: MOTOR B; TerminalBlock_Phoenix_PT-1,5-2-3.5-H_1x02_P3.50mm_Horizontal; MPN 1984617
Q5: AO3401A; SOT-23; MPN AO3401A
R29, R32, R34, R35, R36, R37: 100k; R_0603_1608Metric; MPN RC0603FR-07100KL
R30, R31: 0.25R 1W; R_2512_6332Metric; MPN WSL2512R2500FEA
R33: 10k; R_0603_1608Metric; MPN RC0603FR-0710KL
U7: DRV8833PWPR; HTSSOP-16-1EP_4.4x5mm_P0.65mm_EP3.4x5mm_Mask2.46x2.31mm_The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; MPN DRV8833PWPR

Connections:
+3V3: R33.1; also elsewhere on the board
GND: C32.2, C33.2, C34.2, C35.2, J6.2, R29.2, R30.2, R31.2, R32.2, R34.2, R35.2, R36.2, R37.2, U7.13 (GND), U7.17 (GND); also elsewhere on the board
ISENSE_A: R30.1, U7.3 (AISEN)
ISENSE_B: R31.1, U7.6 (BISEN)
MOTOR_A_N: J7.2, U7.4 (AOUT2)
MOTOR_A_P: J7.1, U7.2 (AOUT1)
MOTOR_B_N: J8.2, U7.5 (BOUT2)
MOTOR_B_P: J8.1, U7.7 (BOUT1)
MOTOR_FUSED: F5.2, Q5.3 (D)
MOTOR_RAW: F5.1, J6.1
M_A1: R34.1, U7.16 (AIN1); also elsewhere on the board
M_A2: R35.1, U7.15 (AIN2); also elsewhere on the board
M_B1: R36.1, U7.9 (BIN1); also elsewhere on the board
M_B2: R37.1, U7.10 (BIN2); also elsewhere on the board
M_FAULT: R33.2, U7.8 (~FAULT); also elsewhere on the board
M_SLEEP: R32.1, U7.1 (~SLEEP); also elsewhere on the board
M_VCP: C31.1, U7.11 (VCP)
M_VINT: C32.1, U7.14 (VINT)
Q5_G: Q5.1 (G), R29.1
VM: C31.2, C33.1, C34.1, C35.1, Q5.2 (S), U7.12 (VM)

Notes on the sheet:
DRV8833PWPR (PowerPAD), not uncooled PW. Rsense=0.25ohm => Itrip typ 0.8A. Recommend <=0.6A continuous each; 3-8.4V motor input. Limit is per bridge, not advertised 2A. Regenerative braking raises VM; use a sink-capable battery supply. Validate VM stays <10.8V in operation, <12V absolute. Fit 100nF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

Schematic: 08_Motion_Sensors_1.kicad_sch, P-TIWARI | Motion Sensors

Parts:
C36, C37, C39, C40, C41: 100nF 16V; C_0603_1608Metric; MPN GRM188R71C104KA01D
C38: 1uF 16V; C_0603_1608Metric; MPN GRM188R61C105KA12D
C42: 4.7uF 10V; C_0603_1608Metric; MPN GRM188R61A475KE15D
U8: LSM6DS3TR-C; LGA-14_3x2.5mm_P0.5mm_LayoutBorder3x4y; MPN LSM6DS3TR-C
U9: LIS3MDLTR; LGA-12_2x2mm_P0.5mm; MPN LIS3MDLTR

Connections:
+3V3_SENS: C36.1, C37.1, C38.1, C39.1, C40.1, C42.1, U8.5 (VDDIO), U8.8 (VDD), U8.12 (CS), U9.5 (Vdd), U9.6 (Vdd_IO), U9.10 (~CS); also elsewhere on the board
GND: C36.2, C37.2, C38.2, C39.2, C40.2, C41.2, C42.2, U8.1 (SDO/SA0), U8.6 (GND), U8.7 (GND), U9.2 (GND), U9.3 (GND), U9.9 (SDO/SA1), U9.12 (GND); also elsewhere on the board
I2C_SCL: U8.13 (SCL), U9.1 (SCL/SPC); also elsewhere on the board
I2C_SDA: U8.14 (SDA), U9.11 (SDA/SDI/SDO); also elsewhere on the board
IMU_INT: U8.4 (INT1); also elsewhere on the board
MAG_C1: C41.1, U9.4 (C1)

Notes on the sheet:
LSM6DS3TR-C uses installed LSM6DS3 symbol: identical 14-pin mapping, 3x2.5mm LGA footprint. IMU I2C 0x6A (SA0=0), INT1 direct GPIO32. Magnetometer I2C 0x1C (SA1=0). LIS3MDL reserved pins 2/12 grounded; C1 100nF. IMU SDx/SCx/INT2 intentionally unused. Calibrate accelerometer, gyro bias and compass h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

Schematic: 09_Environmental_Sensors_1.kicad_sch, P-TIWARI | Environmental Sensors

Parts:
C43, C44, C45: 100nF 16V; C_0603_1608Metric; MPN GRM188R71C104KA01D
U10: BME280; Bosch_LGA-8_2.5x2.5mm_P0.65mm_ClockwisePinNumbering_Board; MPN BME280
U11: VEML7700-TT; VEML7700_TT; MPN VEML7700-TT

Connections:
+3V3_SENS: C43.1, C44.1, C45.1, U10.2 (CSB), U10.6 (VDDIO), U10.8 (VDD), U11.2 (VDD); also elsewhere on the board
GND: C43.2, C44.2, C45.2, U10.1 (GND), U10.5 (SDO), U10.7 (GND), U11.3 (GND); also elsewhere on the board
I2C_SCL: U10.4 (SCK), U11.1 (SCL); also elsewhere on the board
I2C_SDA: U10.3 (SDI), U11.4 (SDA); also elsewhere on the board

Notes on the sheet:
BME280 I2C 0x76; CSB=VDDIO, SDO=GND. VEML7700 fixed 0x10. Keep optical/pressure openings clear. Do not wash MEMS/optical sensors without supplier approval. BME temperature includes PCB self-heating; characterize board-on offsets under Wi-Fi/motor load.

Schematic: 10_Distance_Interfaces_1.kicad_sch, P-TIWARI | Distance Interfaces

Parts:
C46, C47, C49, C51: 100nF 16V; C_0603_1608Metric; MPN GRM188R71C104KA01D
C48: 4.7uF 10V; C_0603_1608Metric; MPN GRM188R61A475KE15D
C50: 100pF 50V; C_0603_1608Metric; MPN GRM1885C1H101JA01D
J9: ULTRASONIC 5V; JST_GH_SM04B-GHS-TB_1x04-1MP_P1.25mm_Horizontal; MPN SM04B-GHS-TB(LF)(SN)
R38, R39: 10k; R_0603_1608Metric; MPN RC0603FR-0710KL
R40: 1k; R_0603_1608Metric; MPN RC0603FR-071KL
R41: 100k; R_0603_1608Metric; MPN RC0603FR-07100KL
U12: VL53L1CXV0FY1; ST_VL53L1x; MPN VL53L1CXV0FY1
U13: SN74LVC1G17DBVR; SOT-23-5; MPN SN74LVC1G17DBVR

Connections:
+3V3: C49.1, U13.5 (VCC); also elsewhere on the board
+3V3_SENS: C46.1, C47.1, C48.1, R38.1, R39.1, U12.1 (AVDDVCSEL), U12.11 (AVDD); also elsewhere on the board
BAT5: C51.1, J9.1; also elsewhere on the board
GND: C46.2, C47.2, C48.2, C49.2, C50.2, C51.2, J9.4, R41.2, U12.2 (AVSSVCSEL), U12.3 (GND), U12.4 (GND), U12.6 (GND), U12.12 (GND), U13.3 (GND); also elsewhere on the board
I2C_SCL: U12.10 (SCL); also elsewhere on the board
I2C_SDA: U12.9 (SDA); also elsewhere on the board
TOF_INT: R39.2, U12.7 (GPIO1); also elsewhere on the board
TOF_XSHUT: R38.2, U12.5 (XSHUT); also elsewhere on the board
US_ECHO: U13.4; also elsewhere on the board
US_ECHO_RAW: J9.3, R40.1
US_ECHO_RC: C50.1, R40.2, R41.1, U13.2
US_TRIG5: J9.2; also elsewhere on the board

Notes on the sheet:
VL53L1X at 0x29: AVDD=3V3_SENS; program 2V8 IO mode with ST driver. XSHUT open-drain control only. DNC pin8 intentionally open. Aperture faces upward: mount board to suit sensing direction. Ultrasonic VCC is battery-derived BAT5: USB-only operation does not power 5V accessories. Echo uses 5.5V-tole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

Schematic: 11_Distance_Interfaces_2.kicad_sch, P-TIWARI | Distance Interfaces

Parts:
U14: SN74AHCT125PWR; TSSOP-14_4.4x5mm_P0.65mm; MPN SN74AHCT125PWR

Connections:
BAT5: U14.14 (VCC); also elsewhere on the board
GND: U14.1, U14.7 (GND); also elsewhere on the board
SERVO_OE: U14.4, U14.10, U14.13; also elsewhere on the board
SERVO_PWM0: U14.5; also elsewhere on the board
SERVO_PWM1: U14.9; also elsewhere on the board
SERVO_PWM2: U14.12; also elsewhere on the board
SERVO_SIG0: U14.6; also elsewhere on the board
SERVO_SIG1: U14.8; also elsewhere on the board
SERVO_SIG2: U14.11; also elsewhere on the board
US_TRIG: U14.2; also elsewhere on the board
US_TRIG5: U14.3; also elsewhere on the board

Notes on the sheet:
VL53L1X at 0x29: AVDD=3V3_SENS; program 2V8 IO mode with ST driver. XSHUT open-drain control only. DNC pin8 intentionally open. Aperture faces upward: mount board to suit sensing direction. Ultrasonic VCC is battery-derived BAT5: USB-only operation does not power 5V accessories. Echo uses 5.5V-tole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

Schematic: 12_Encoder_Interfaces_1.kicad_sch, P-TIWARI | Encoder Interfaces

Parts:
C52, C54, C56, C58: 100nF 16V; C_0603_1608Metric; MPN GRM188R71C104KA01D
C53, C55, C57: 100pF 50V; C_0603_1608Metric; MPN GRM1885C1H101JA01D
J10: ENC LEFT; JST_GH_SM04B-GHS-TB_1x04-1MP_P1.25mm_Horizontal; MPN SM04B-GHS-TB(LF)(SN)
J11: ENC RIGHT; JST_GH_SM04B-GHS-TB_1x04-1MP_P1.25mm_Horizontal; MPN SM04B-GHS-TB(LF)(SN)
R42, R44, R46, R48: 1k; R_0603_1608Metric; MPN RC0603FR-071KL
R43, R45, R47: 10k; R_0603_1608Metric; MPN RC0603FR-0710KL
U15, U16, U17, U18: SN74LVC1G17DBVR; SOT-23-5; MPN SN74LVC1G17DBVR

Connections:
+3V3: C52.1, C54.1, C56.1, C58.1, J10.1, J11.1, R43.1, R45.1, R47.1, U15.5 (VCC), U16.5 (VCC), U17.5 (VCC), U18.5 (VCC); also elsewhere on the board
ENC_LA: U15.4; also elsewhere on the board
ENC_LA_RAW: J10.3, R42.1, R43.2
ENC_LA_RAW_RC: C53.1, R42.2, U15.2
ENC_LB: U16.4; also elsewhere on the board
ENC_LB_RAW: J10.4, R44.1, R45.2
ENC_LB_RAW_RC: C55.1, R44.2, U16.2
ENC_RA: U17.4; also elsewhere on the board
ENC_RA_RAW: J11.3, R46.1, R47.2
ENC_RA_RAW_RC: C57.1, R46.2, U17.2
ENC_RB: U18.4; also elsewhere on the board
ENC_RB_RAW: J11.4, R48.1; also elsewhere on the board
ENC_RB_RAW_RC: R48.2, U18.2; also elsewhere on the board
GND: C52.2, C53.2, C54.2, C55.2, C56.2, C57.2, C58.2, J10.2, J11.2, U15.3 (GND), U16.3 (GND), U17.3 (GND), U18.3 (GND); also elsewhere on the board

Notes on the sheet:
Encoder connectors supply 3V3; push-pull or open-collector inputs accepted. A/B inputs buffer-rated 0-5.5V, with 1k/100pF RC (~100ns) and 10k pullups. GPIO36/39 left, GPIO34/35 right. Use ESP32 PCNT; no reliance on missing internal pullups. External 5V encoder supply allowed only with shared ground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

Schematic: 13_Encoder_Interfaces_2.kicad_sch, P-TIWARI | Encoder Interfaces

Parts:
C59: 100pF 50V; C_0603_1608Metric; MPN GRM1885C1H101JA01D
R49: 10k; R_0603_1608Metric; MPN RC0603FR-0710KL

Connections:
+3V3: R49.1; also elsewhere on the board
ENC_RB_RAW: R49.2; also elsewhere on the board
ENC_RB_RAW_RC: C59.1; also elsewhere on the board
GND: C59.2; also elsewhere on the board

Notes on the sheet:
Encoder connectors supply 3V3; push-pull or open-collector inputs accepted. A/B inputs buffer-rated 0-5.5V, with 1k/100pF RC (~100ns) and 10k pullups. GPIO36/39 left, GPIO34/35 right. Use ESP32 PCNT; no reliance on missing internal pullups. External 5V encoder supply allowed only with shared ground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
